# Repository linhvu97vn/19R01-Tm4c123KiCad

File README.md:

# tm4cboard
A design board for tm4c123gh6pm using KiCad

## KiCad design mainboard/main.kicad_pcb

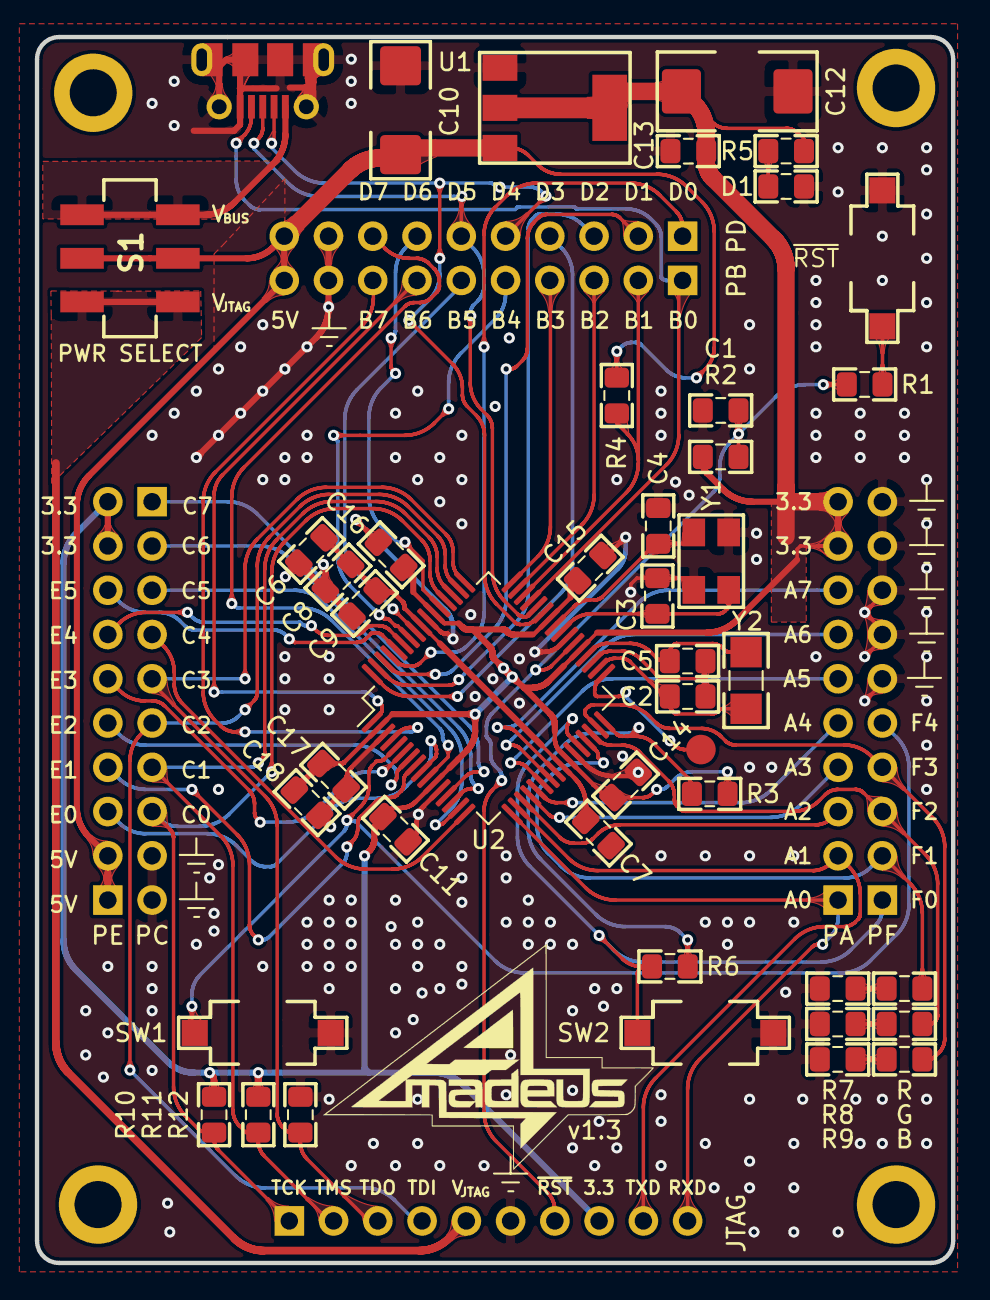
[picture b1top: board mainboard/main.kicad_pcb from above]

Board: 2 copper layers, 52.6 x 70.4 mm, 54 parts (0 on the bottom side), 61 nets.

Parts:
B: LED; LED_0805_2012Metric_Pad1.15x1.40mm_HandSolder
C1, C6, C7, C11, C13, C14, C16: 0.1uF; C_0805_2012Metric_Pad1.15x1.40mm_HandSolder
C2, C5: 24pF; C_0805_2012Metric_Pad1.15x1.40mm_HandSolder
C3, C4: 10pF; C_0805_2012Metric_Pad1.15x1.40mm_HandSolder
C8, C17: 1uF; C_0805_2012Metric_Pad1.15x1.40mm_HandSolder
C9: 2.2uF; C_0805_2012Metric_Pad1.15x1.40mm_HandSolder
C10: 10uF; tantalum6032
C12: 22uF; tantalum7343
C15, C18: 0.01uF; C_0805_2012Metric_Pad1.15x1.40mm_HandSolder
D1: LED; LED_0805_2012Metric_Pad1.15x1.40mm_HandSolder
G: LED; LED_0805_2012Metric_Pad1.15x1.40mm_HandSolder
H1, H2, H3, H4: MountingHole; MountingHole_2.7mm_M2.5_ISO14580_Pad
J1: USB_OTG; USB_Micro-B_Molex
J2: HIB; PinHeader_1x01_P2.54mm_Vertical
JTAG: JTAG Port; PinHeader_1x10_P2.54mm_Vertical
PA: A Port; PinHeader_1x10_P2.54mm_Vertical
PB: B Port; PinHeader_1x10_P2.54mm_Vertical
PD: D Port; PinHeader_1x10_P2.54mm_Vertical
PE: E Port; PinHeader_1x10_P2.54mm_Vertical
PF: F Port; PinHeader_1x10_P2.54mm_Vertical
PWR SELECT: PC; PinHeader_1x10_P2.54mm_Vertical
R: LED; LED_0805_2012Metric_Pad1.15x1.40mm_HandSolder
R1: 470; R_0805_2012Metric_Pad1.15x1.40mm_HandSolder
R2, R10, R11, R12: 10k; R_0805_2012Metric_Pad1.15x1.40mm_HandSolder
R3: 1m; R_0805_2012Metric_Pad1.15x1.40mm_HandSolder
R4: 220; R_0805_2012Metric_Pad1.15x1.40mm_HandSolder
R5, R6, R7, R8, R9: 330; R_0805_2012Metric_Pad1.15x1.40mm_HandSolder
S1: JS202011SCQN; Slide_Switch_2.54mm
SW1, SW2: SW_Push; Buttons
U1: LM1117-3.3; LM1117-3.3V
U2: TM4C123GH6PM; TMC123GH6PM
Y1: Crystal_GND24_Small; Crystal_SMD_5032-4Pin_5.0x3.2mm
Y2: Crystal-32.768KHz; Crystal_SMD_MicroCrystal_CC7V-T1A-2Pin_3.2x1.5mm_HandSolder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

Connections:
+3V3: C11.1, C12.1, C13.1, C14.1, C15.1, C16.1, C17.1, C18.1, JTAG.8, PA.9, PA.10, PE.9, PE.10, R2.1, R3.2, R5.1, R10.1, R11.1, U1.2, U1.4, U2.2, U2.11, U2.26, U2.37, U2.42, U2.54
+5V: C10.1, PB.10, PD.10, PE.1, PE.2, R4.2, S1.2, S1.5, U1.3
/D+: J1.3, PD.6, U2.44
/D-: J1.2, PD.5, U2.43
/GNDX: C2.2, C5.1, U2.35
/PA0: JTAG.10, PA.1, U2.17
/PA1: JTAG.9, PA.2, U2.18
/PA2: PA.3, U2.19
/PA3: PA.4, U2.20
/PA4: PA.5, U2.21
/PA5: PA.6, U2.22
/PA6: PA.7, U2.23
/PA7: PA.8, U2.24
/PB0: J1.4, PB.1, U2.45
/PB1: PB.2, R4.1, U2.46
/PB2: PB.3, U2.47
/PB3: PB.4, U2.48
/PB4: PB.5, U2.58
/PB5: PB.6, U2.57
/PB6: PB.7, U2.1
/PB7: PB.8, U2.4
/PC0: JTAG.1, PWR SELECT.8, R10.2, U2.52
/PC1: JTAG.2, PWR SELECT.7, R11.2, U2.51
/PC2: JTAG.4, PWR SELECT.6, U2.50
/PC3: JTAG.3, PWR SELECT.5, R12.2, U2.49
/PC4: PWR SELECT.4, U2.16
/PC5: PWR SELECT.3, U2.15
/PC6: PWR SELECT.2, U2.14
/PC7: PWR SELECT.1, U2.13
/PD0: PD.1, U2.61
/PD1: PD.2, U2.62
/PD2: PD.3, U2.63
/PD3: PD.4, U2.64
/PD6: PD.7, U2.53
/PD7: PD.8, U2.10
/PE0: PE.3, U2.9
/PE1: PE.4, U2.8
/PE2: PE.5, U2.7
/PE3: PE.6, U2.6
/PE4: PE.7, U2.59
/PE5: PE.8, U2.60
/PF0: PF.1, R6.1, SW2.1, U2.28
/PF1: PF.2, R.2, U2.29
/PF2: G.2, PF.3, U2.30
/PF3: B.2, PF.4, U2.31
/PF4: PF.5, SW1.1, U2.5
/VDEBUG: JTAG.5, S1.3, S1.4
/~RESET: C1.2, JTAG.7, R1.1, R2.2, U2.38
/~WAKE: R3.1, R6.2, U2.32
Earth: C1.1, C3.1, C4.2, C6.2, C7.2, C8.2, C9.2, C10.2, C11.2, C12.2, C13.2, C14.2, C15.2, C16.2, C17.2, C18.2, D1.1, J1.5, J1.6, JTAG.6, PB.9, PD.9, PF.6, PF.7, PF.8, PF.9, PF.10, PWR SELECT.9, PWR SELECT.10, R7.1, R8.1, R9.1, R12.1, SW1.2, SW2.2, U1.1, U2.3, U2.12, U2.27, U2.39, U2.55, Y1.2, Y1.4
unnamed: C2.1, U2.34, Y2.1
unnamed: C3.2, U2.40, Y1.1
unnamed: C4.1, U2.41, Y1.3
unnamed: C5.2, U2.36, Y2.2
unnamed: C6.1, C7.1, C8.1, C9.1, U2.25, U2.56
unnamed: D1.2, R5.2
unnamed: R.1, R7.2
unnamed: G.1, R8.2
unnamed: B.1, R9.2
unnamed: J2.1, U2.33
VBUS: J1.1, S1.1, S1.6

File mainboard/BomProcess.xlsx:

| Sourced | Placed | References | Value | Footprint | Quantity
1 | X |  | C10 | 10uF | CP_Elec_4x5.4 | 1 |  |  |  |  | pF | nF | uF
2 |  |  | C12 | 22uF | CP_Elec_4x5.4 | 1 |  |  | ????
3 | X |  | C9 | 2.2uF | C_0805_2012Metric_Pad1.15x1.40mm_HandSolder | 1
4 | X |  | R1 | 470 | R_0805_2012Metric_Pad1.15x1.40mm_HandSolder | 1
5 | X |  | R3 | 1m | R_0805_2012Metric_Pad1.15x1.40mm_HandSolder | 1
6 | X |  | R4 | 220 | R_0805_2012Metric_Pad1.15x1.40mm_HandSolder | 1
7 | X |  | U1 | LM1117-3.3 | LM1117-3.3V | 1 |  |  |  | x5 | 1. Thạnh anh 16 Mhz, SMD loại 4 chân, kích thước 3.2x2.5 mm (3225)
8 | X |  | U2 | TM4C123GH6PM | TMC123GH6PM | 1 |  |  |  | x5 | 2. Thạch anh 32.768kHz, SMD loại 2 chân, kích thước 3.2x1.5mm (3215)
9 |  |  | Y1 | Crystal_GND24_Small | Crystal_SMD_3225-4Pin_3.2x2.5mm | 1 |  |  |  | x5 | 3. Tụ phân cực, SMD, 22uF, 4x5.4
10 |  |  | Y2 | Crystal-32.768KHz | Crystal_SMD_MicroCrystal_CC7V-T1A-2Pin_3.2x1.5mm_HandSoldering | 1 |  |  |  | x10 | 4. Tụ không phân cực, SMD, 24pF, 0805
11 | X |  | JTAG | JTAG Port | PinHeader_1x10_P2.54mm_Vertical | 1 |  |  |  | x1 | 5. Biến trở loại 1k Ohm
12 | X |  | PA | A Port | PinHeader_1x10_P2.54mm_Vertical | 1
13 | X |  | PB | B Port | PinHeader_1x10_P2.54mm_Vertical | 1
14 | X |  | PD | D Port | PinHeader_1x10_P2.54mm_Vertical | 1
15 | X |  | PE | E Port | PinHeader_1x10_P2.54mm_Vertical | 1
16 | X |  | PF | F Port | PinHeader_1x10_P2.54mm_Vertical | 1
17 | X |  | S1 | JS202011SCQN | Slide_Switch_2.54mm | 1
18 | X |  | J2 | HIB | PinHeader_1x01_P2.54mm_Vertical | 1
19 | X |  | J4 | PC | PinHeader_1x10_P2.54mm_Vertical | 1
20 | X |  | J1 | USB_OTG | USB_Micro-B_Molex | 1
21 |  |  | C2, C5 | 24pF | C_0805_2012Metric_Pad1.15x1.40mm_HandSolder | 2 |  |  | ????
22 | X |  | C3, C4 | 10pF | C_0805_2012Metric_Pad1.15x1.40mm_HandSolder | 2
23 | X |  | C8, C17 | 1uF | C_0805_2012Metric_Pad1.15x1.40mm_HandSolder | 2
24 | X |  | C15, C18 | 0.01uF | C_0805_2012Metric_Pad1.15x1.40mm_HandSolder | 2
25 | X |  | SW1, SW2, ~RST | SW_Push | Buttons | 3
26 | X |  | R2, R10, R11, R12 | 10k | R_0805_2012Metric_Pad1.15x1.40mm_HandSolder | 4
27 | X |  | B, D1, G, R | LED | LED_0805_2012Metric_Pad1.15x1.40mm_HandSolder | 4
28 | X |  | R5, R6, R7, R8, R9 | 330 | R_0805_2012Metric_Pad1.15x1.40mm_HandSolder | 5
29 | X |  | C1, C6, C7, C11, C13, C14, C16 | 0.1uF | C_0805_2012Metric_Pad1.15x1.40mm_HandSolder | 7

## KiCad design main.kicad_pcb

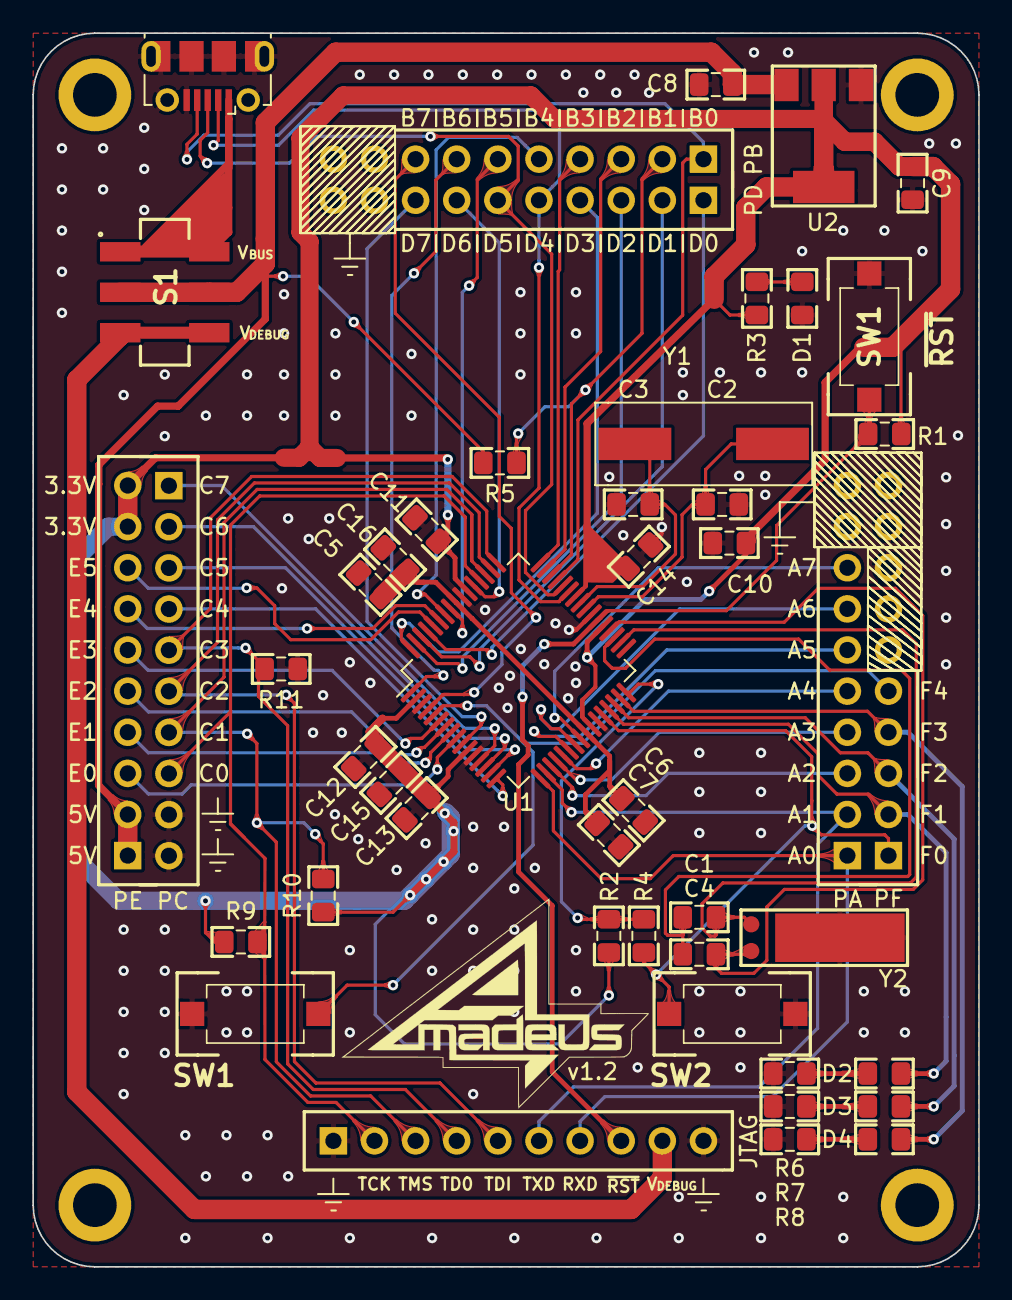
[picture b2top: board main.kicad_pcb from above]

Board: 2 copper layers, 58.4 x 76.2 mm, 51 parts (0 on the bottom side), 60 nets.

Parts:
C1, C4: 24pF; C_0805_2012Metric_Pad1.15x1.40mm_HandSolder
C2, C3: 10pF; C_0805_2012Metric_Pad1.15x1.40mm_HandSolder
C5, C14: 1uF; C_0805_2012Metric_Pad1.15x1.40mm_HandSolder
C6, C10, C12, C15: 0.01uF; C_0805_2012Metric_Pad1.15x1.40mm_HandSolder
C7, C11, C13: 0.1uF; C_0805_2012Metric_Pad1.15x1.40mm_HandSolder
C8: 10uF; C_0805_2012Metric_Pad1.15x1.40mm_HandSolder
C9: 22uF; C_0805_2012Metric_Pad1.15x1.40mm_HandSolder
C16: 2.2uF; C_0805_2012Metric_Pad1.15x1.40mm_HandSolder
D1, D2, D3, D4: LED; LED_0805_2012Metric_Pad1.15x1.40mm_HandSolder
H1, H2, H3, H4: MountingHole; MountingHole_2.7mm_M2.5_ISO14580_Pad
J1: USB_OTG; USB_Micro-B_Molex
JTAG: JTAG Port; PinHeader_1x10_P2.54mm_Vertical
PA: A Port; PinHeader_1x10_P2.54mm_Vertical
PB: B Port; PinHeader_1x10_P2.54mm_Vertical
PC: C Port; PinHeader_1x10_P2.54mm_Vertical
PD: D Port; PinHeader_1x10_P2.54mm_Vertical
PE: E Port; PinHeader_1x10_P2.54mm_Vertical
PF: F Port; PinHeader_1x10_P2.54mm_Vertical
R1, R9, R10, R11: 10k; R_0805_2012Metric_Pad1.15x1.40mm_HandSolder
R2: 1m; R_0805_2012Metric_Pad1.15x1.40mm_HandSolder
R3: 470; R_0805_2012Metric_Pad1.15x1.40mm_HandSolder
R4, R6, R7, R8: 330; R_0805_2012Metric_Pad1.15x1.40mm_HandSolder
R5: 220; R_0805_2012Metric_Pad1.15x1.40mm_HandSolder
S1: JS202011SCQN; Slide_Switch_2.54mm
SW1: ~RST; Buttons
SW1#2, SW2: SW_Push; Buttons
U1: TM4C123GH6PM; TMC123GH6PM
U2: LM1117-3.3; LM1117-3.3V
Y1: Crystal-16MHz; Crystal_SMD_HC49-SD
Y2: Crystal-32.768KHz; Crystal_C38-LF_D3.0mm_L8.0mm_Horizontal_1EP_style1

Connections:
+3V3: C9.1, C10.1, C11.1, C12.1, C13.1, C14.1, C15.1, PE.9, PE.10, R1.1, R2.2, R3.1, R9.1, R10.1, U1.2, U1.11, U1.26, U1.37, U1.42, U1.54, U2.2, U2.4
+5V: C8.1, PE.1, PE.2, R5.2, S1.2, S1.5, U2.3
/GNDX: C1.2, C4.1, U1.35
/PA0: JTAG.7, PA.1, U1.17
/PA1: JTAG.6, PA.2, U1.18
/PA2: PA.3, U1.19
/PA3: PA.4, U1.20
/PA4: PA.5, U1.21
/PA5: PA.6, U1.22
/PA6: PA.7, U1.23
/PA7: PA.8, U1.24
/PB0: J1.4, PB.1, U1.45
/PB1: PB.2, R5.1, U1.46
/PB2: PB.3, U1.47
/PB3: PB.4, U1.48
/PB4: PB.5, U1.58
/PB5: PB.6, U1.57
/PB6: PB.7, U1.1
/PB7: PB.8, U1.4
/PC0: JTAG.2, PC.8, R9.2, U1.52
/PC1: JTAG.3, PC.7, R10.2, U1.51
/PC2: JTAG.5, PC.6, U1.50
/PC3: JTAG.4, PC.5, R11.2, U1.49
/PC4: PC.4, U1.16
/PC5: PC.3, U1.15
/PC6: PC.2, U1.14
/PC7: PC.1, U1.13
/PD0: PD.1, U1.61
/PD1: PD.2, U1.62
/PD2: PD.3, U1.63
/PD3: PD.4, U1.64
/PD4: J1.2, PD.5, U1.43
/PD5: J1.3, PD.6, U1.44
/PD6: PD.7, U1.53
/PD7: PD.8, U1.10
/PE0: PE.3, U1.9
/PE1: PE.4, U1.8
/PE2: PE.5, U1.7
/PE3: PE.6, U1.6
/PE4: PE.7, U1.59
/PE5: PE.8, U1.60
/PF0: PF.1, R4.1, SW2.1, U1.28
/PF1: D2.2, PF.2, U1.29
/PF2: D3.2, PF.3, U1.30
/PF3: D4.2, PF.4, U1.31
/PF4: PF.5, SW1#2.1, U1.5
/VDEBUG: JTAG.9, S1.3, S1.4
/~RESET: JTAG.8, R1.2, SW1.1, U1.38
/~WAKE: R2.1, R4.2, U1.32
Earth: C2.1, C3.2, C5.2, C6.2, C7.2, C8.2, C9.2, C10.2, C11.2, C12.2, C13.2, C14.2, C15.2, C16.2, D1.1, J1.5, J1.6, JTAG.1, JTAG.10, PA.9, PA.10, PB.9, PB.10, PC.9, PC.10, PD.9, PD.10, PF.6, PF.7, PF.8, PF.9, PF.10, R6.1, R7.1, R8.1, R11.1, SW1.2, SW1#2.2, SW2.2, U1.3, U1.12, U1.27, U1.39, U1.55, U2.1, Y2.3
unnamed: C1.1, U1.34, Y2.2
unnamed: C2.2, U1.40, Y1.1
unnamed: C3.1, U1.41, Y1.2
unnamed: C4.2, U1.36, Y2.1
unnamed: C5.1, C6.1, C7.1, C16.1, U1.25, U1.56
unnamed: D1.2, R3.2
unnamed: D2.1, R6.2
unnamed: D3.1, R7.2
unnamed: D4.1, R8.2
VBUS: J1.1, S1.1, S1.6

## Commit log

2020-01-02 main files
2020-01-03 Updated
    Cập nhật lại điện trở treo cho JTAG
    Thay thạch anh SMD thành loại dễ tìm hơn
2020-01-04 Updated a little
2020-01-05 Rounder for tracks
2020-01-29 Updated v1.3
